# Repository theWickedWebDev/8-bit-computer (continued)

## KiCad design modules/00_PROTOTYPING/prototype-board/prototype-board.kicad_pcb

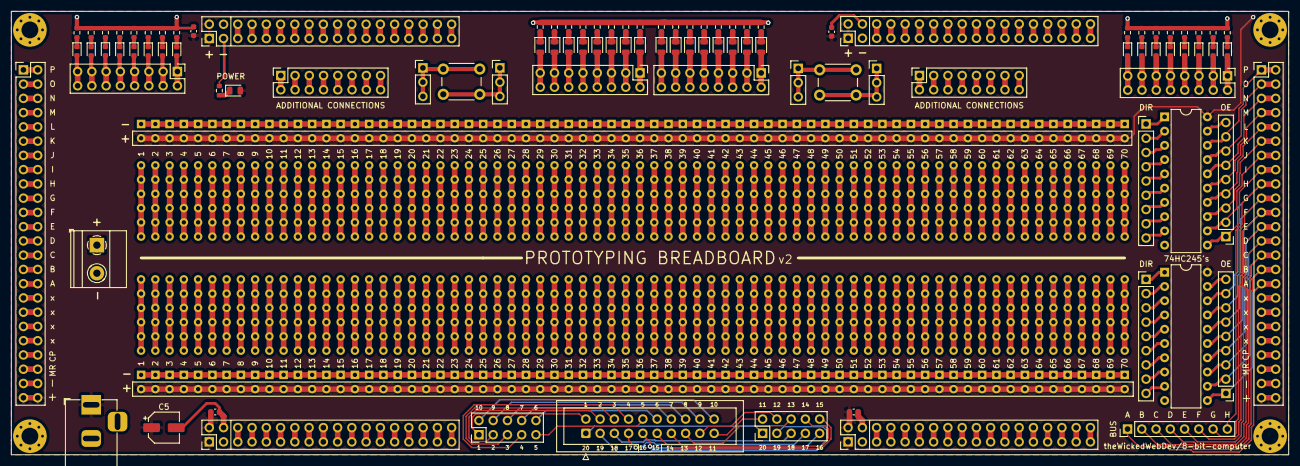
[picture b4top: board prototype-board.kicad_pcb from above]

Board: 2 copper layers, 227.6 x 79.0 mm, 104 parts (0 on the bottom side), 235 nets.

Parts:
C2, C3, C4, C6: 0603B103K500NT; C_0603_1608Metric
C5: SMD-ECAP-5x5.8; CP_Elec_5x5.8
D1, D2, D3, D4, D5, D6, D7, D8, D9, D10, D11, D12, D13, D14, D15, D16, D33: NCD0805R1; LED_0805_2012Metric
D17, D18, D19, D20, D21, D22, D23, D24, D25, D26, D27, D28, D29, D30, D31, D32: 19-217/BHC-ZL1M2RY/3T; LED_0603_1608Metric
J1, J2, J3, J4: Conn_02x08_Male; PinHeader_2x08_P2.54mm_Vertical
J5, J6, J14, J15: Conn_02x18_Odd_Even; PinHeader_2x18_P2.54mm_Vertical
J7: Barrel_Jack; BarrelJack_Horizontal
J8, J9: Conn_02x24_Odd_Even; PinHeader_2x24_P2.54mm_Vertical
J10, J11, J12, J13: Conn_01x09_Male; PinHeader_1x09_P2.54mm_Vertical
J16, J17: Screw_Terminal_02x08; PinSocket_2x08_P2.54mm_Vertical
J18: Screw_Terminal_01x02; TerminalBlock_Phoenix_MKDS-1,5-2_1x02_P5.00mm_Horizontal
J19, J20, J25, J26: Conn_01x03_Male; PinHeader_1x03_P2.54mm_Vertical
J21: Conn_02x20_Odd_Even; IDC-Header_2x10_P2.54mm_Vertical
J22, J23: Conn_02x05_Odd_Even; PinHeader_2x05_P2.54mm_Vertical
J24: Conn_01x08_Male; PinHeader_1x08_P2.54mm_Vertical
SW1, SW2: SW_Push; SW_PUSH_6mm
U1: 6X70X2_breadboard; 6x70
U2, U3: power-rail-breadboard; power-rail-70
U4, U5, U6, U7, U8, U9, U10, U11, U12, U13, U14, U15, U16, U17, U18, U19, U20, U21, U22, U23, U24, U25, U26, U27, U28, U29, U30, U31, U32, U33, U34, U35, U36: 0603WAF1001T5E; R_0603_1608Metric
U39, U68: 74LS245; DIP-20_W7.62mm

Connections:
GND: C2.2, C3.2, C4.2, C5.2, C6.2, J5.3, J5.4, J6.3, J6.4, J7.2, J8.45, J8.46, J9.45, J9.46, J14.3, J14.4, J15.3, J15.4, J18.2, U2.-, U3.-, U4.2, U5.2, U6.2, U7.2, U8.2, U9.2, U10.2, U11.2, U12.2, U13.2, U14.2, U15.2, U16.2, U17.2, U18.2, U19.2, U20.2, U21.2, U22.2, U23.2, U24.2, U25.2, U26.2, U27.2, U28.2, U29.2, U30.2, U31.2, U32.2, U33.2, U34.2, U35.2, U36.2, U39.10, U68.10
unnamed: D1.1, U5.1
unnamed: D1.2, J1.15, J1.16
unnamed: D2.1, U7.1
unnamed: D2.2, J1.13, J1.14
unnamed: D3.1, U9.1
unnamed: D3.2, J1.11, J1.12
unnamed: D4.1, U11.1
unnamed: D4.2, J1.9, J1.10
unnamed: D5.1, U13.1
unnamed: D5.2, J1.7, J1.8
unnamed: D6.1, U15.1
unnamed: D6.2, J1.5, J1.6
unnamed: D7.1, U17.1
unnamed: D7.2, J1.3, J1.4
unnamed: D8.1, U19.1
unnamed: D8.2, J1.1, J1.2
unnamed: D9.1, U4.1
unnamed: D9.2, J2.15, J2.16
unnamed: D10.1, U6.1
unnamed: D10.2, J2.13, J2.14
unnamed: D11.1, U8.1
unnamed: D11.2, J2.11, J2.12
unnamed: D12.1, U10.1
unnamed: D12.2, J2.9, J2.10
unnamed: D13.1, U12.1
unnamed: D13.2, J2.7, J2.8
unnamed: D14.1, U14.1
unnamed: D14.2, J2.5, J2.6
unnamed: D15.1, U16.1
unnamed: D15.2, J2.3, J2.4
unnamed: D16.1, U18.1
unnamed: D16.2, J2.1, J2.2
unnamed: D17.1, U20.1
unnamed: D17.2, J3.15, J3.16
unnamed: D18.1, U21.1
unnamed: D18.2, J3.13, J3.14
unnamed: D19.1, U22.1
unnamed: D19.2, J3.11, J3.12
unnamed: D20.1, U23.1
unnamed: D20.2, J3.9, J3.10
unnamed: D21.1, U24.1
unnamed: D21.2, J3.7, J3.8
unnamed: D22.1, U25.1
unnamed: D22.2, J3.5, J3.6
unnamed: D23.1, U26.1
unnamed: D23.2, J3.3, J3.4
unnamed: D24.1, U27.1
unnamed: D24.2, J3.1, J3.2
unnamed: D25.1, U28.1
unnamed: D25.2, J4.15, J4.16
unnamed: D26.1, U29.1
unnamed: D26.2, J4.13, J4.14
unnamed: D27.1, U30.1
unnamed: D27.2, J4.11, J4.12
unnamed: D28.1, U31.1
unnamed: D28.2, J4.9, J4.10
unnamed: D29.1, U32.1
unnamed: D29.2, J4.7, J4.8
unnamed: D30.1, U33.1
unnamed: D30.2, J4.5, J4.6
unnamed: D31.1, U34.1
unnamed: D31.2, J4.3, J4.4
unnamed: D32.1, U35.1
unnamed: D32.2, J4.1, J4.2
unnamed: D33.1, U36.1
unnamed: J5.5, J5.6
unnamed: J5.7, J5.8
unnamed: J5.9, J5.10
unnamed: J5.11, J5.12
unnamed: J5.13, J5.14
unnamed: J5.15, J5.16
unnamed: J5.17, J5.18
unnamed: J5.19, J5.20
unnamed: J5.21, J5.22
unnamed: J5.23, J5.24
unnamed: J5.25, J5.26
unnamed: J5.27, J5.28
unnamed: J5.29, J5.30
unnamed: J5.31, J5.32
unnamed: J5.33, J5.34
unnamed: J5.35, J5.36
unnamed: J6.5, J6.6
unnamed: J6.7, J6.8
unnamed: J6.9, J6.10
unnamed: J6.11, J6.12
unnamed: J6.13, J6.14
unnamed: J6.15, J6.16
unnamed: J6.17, J6.18
unnamed: J6.19, J6.20
unnamed: J6.21, J6.22
unnamed: J6.23, J6.24
unnamed: J6.25, J6.26
unnamed: J6.27, J6.28
unnamed: J6.29, J6.30
unnamed: J6.31, J6.32
unnamed: J6.33, J6.34
unnamed: J6.35, J6.36
unnamed: J8.33, J8.34
unnamed: J8.35, J8.36
unnamed: J8.37, J8.38
unnamed: J8.39, J8.40
unnamed: J8.41, J8.42
unnamed: J8.43, J8.44
unnamed: J9.1, J9.2
unnamed: J9.3, J9.4
unnamed: J9.5, J9.6
unnamed: J9.7, J9.8
unnamed: J9.9, J9.10
unnamed: J9.11, J9.12
unnamed: J9.13, J9.14
unnamed: J9.15, J9.16
unnamed: J9.17, J9.18
unnamed: J9.19, J9.20
unnamed: J9.21, J9.22
unnamed: J9.23, J9.24
unnamed: J9.25, J9.26
unnamed: J9.27, J9.28
unnamed: J9.29, J9.30
unnamed: J9.31, J9.32
unnamed: J9.33, J9.34
unnamed: J9.35, J9.36
unnamed: J9.37, J9.38
unnamed: J9.39, J9.40
unnamed: J9.41, J9.42
unnamed: J9.43, J9.44
unnamed: J10.1, U68.1
unnamed: J10.2, U68.2
unnamed: J10.3, U68.3
unnamed: J10.4, U68.4
unnamed: J10.5, U68.5
unnamed: J10.6, U68.6
unnamed: J10.7, U68.7
unnamed: J10.8, U68.8
unnamed: J10.9, U68.9
unnamed: J8.15, J8.16, J11.1, U68.11
unnamed: J8.13, J8.14, J11.2, U68.12
unnamed: J8.11, J8.12, J11.3, U68.13
unnamed: J8.9, J8.10, J11.4, U68.14
unnamed: J8.7, J8.8, J11.5, U68.15
unnamed: J8.5, J8.6, J11.6, U68.16
unnamed: J8.3, J8.4, J11.7, U68.17
unnamed: J8.1, J8.2, J11.8, U68.18
unnamed: J11.9, U68.19
unnamed: J12.1, U39.1
unnamed: J12.2, U39.2
unnamed: J12.3, U39.3
unnamed: J12.4, U39.4
unnamed: J12.5, U39.5
unnamed: J12.6, U39.6
unnamed: J12.7, U39.7
unnamed: J12.8, U39.8
unnamed: J12.9, U39.9
unnamed: J8.31, J8.32, J13.1, J24.1, U39.11
unnamed: J8.29, J8.30, J13.2, J24.2, U39.12
unnamed: J8.27, J8.28, J13.3, J24.3, U39.13
unnamed: J8.25, J8.26, J13.4, J24.4, U39.14
unnamed: J8.23, J8.24, J13.5, J24.5, U39.15
unnamed: J8.21, J8.22, J13.6, J24.6, U39.16
unnamed: J8.19, J8.20, J13.7, J24.7, U39.17
unnamed: J8.17, J8.18, J13.8, J24.8, U39.18
unnamed: J13.9, U39.19
unnamed: J14.5, J14.6
unnamed: J14.7, J14.8
unnamed: J14.9, J14.10
unnamed: J14.11, J14.12
unnamed: J14.13, J14.14
unnamed: J14.15, J14.16
unnamed: J14.17, J14.18
unnamed: J14.19, J14.20
unnamed: J14.21, J14.22
unnamed: J14.23, J14.24
unnamed: J14.25, J14.26
unnamed: J14.27, J14.28
unnamed: J14.29, J14.30
unnamed: J14.31, J14.32
unnamed: J14.33, J14.34
unnamed: J14.35, J14.36
unnamed: J15.5, J15.6
unnamed: J15.7, J15.8
unnamed: J15.9, J15.10
unnamed: J15.11, J15.12
unnamed: J15.13, J15.14
unnamed: J15.15, J15.16
unnamed: J15.17, J15.18
unnamed: J15.19, J15.20
unnamed: J15.21, J15.22
unnamed: J15.23, J15.24
unnamed: J15.25, J15.26
unnamed: J15.27, J15.28
unnamed: J15.29, J15.30
unnamed: J15.31, J15.32
unnamed: J15.33, J15.34
unnamed: J15.35, J15.36
unnamed: J16.1, J16.2
unnamed: J16.3, J16.4
unnamed: J16.5, J16.6
unnamed: J16.7, J16.8
unnamed: J16.9, J16.10
unnamed: J16.11, J16.12
unnamed: J16.13, J16.14
unnamed: J16.15, J16.16
unnamed: J17.1, J17.2
unnamed: J17.3, J17.4
unnamed: J17.5, J17.6
unnamed: J17.7, J17.8
unnamed: J17.9, J17.10
unnamed: J17.11, J17.12
unnamed: J17.13, J17.14
unnamed: J17.15, J17.16
unnamed: J19.1, J19.2, J19.3, SW1.2
unnamed: J20.1, J20.2, J20.3, SW1.1
unnamed: J21.1, J23.1
unnamed: J21.2, J22.1
unnamed: J21.3, J23.3
unnamed: J21.4, J22.3
unnamed: J21.5, J23.5
unnamed: J21.6, J22.5
unnamed: J21.7, J23.7
unnamed: J21.8, J22.7
unnamed: J21.9, J23.9
unnamed: J21.10, J22.9
unnamed: J21.11, J23.10
unnamed: J21.12, J22.10
unnamed: J21.13, J23.8
unnamed: J21.14, J22.8
unnamed: J21.15, J23.6
unnamed: J21.16, J22.6
unnamed: J21.17, J23.4
unnamed: J21.18, J22.4
unnamed: J21.19, J23.2
unnamed: J21.20, J22.2
unnamed: J25.1, J25.2, J25.3, SW2.1
unnamed: J26.1, J26.2, J26.3, SW2.2
VCC: C2.1, C3.1, C4.1, C5.1, C6.1, D33.2, J5.1, J5.2, J6.1, J6.2, J7.1, J8.47, J8.48, J9.47, J9.48, J14.1, J14.2, J15.1, J15.2, J18.1, U2.+, U3.+, U39.20, U68.20

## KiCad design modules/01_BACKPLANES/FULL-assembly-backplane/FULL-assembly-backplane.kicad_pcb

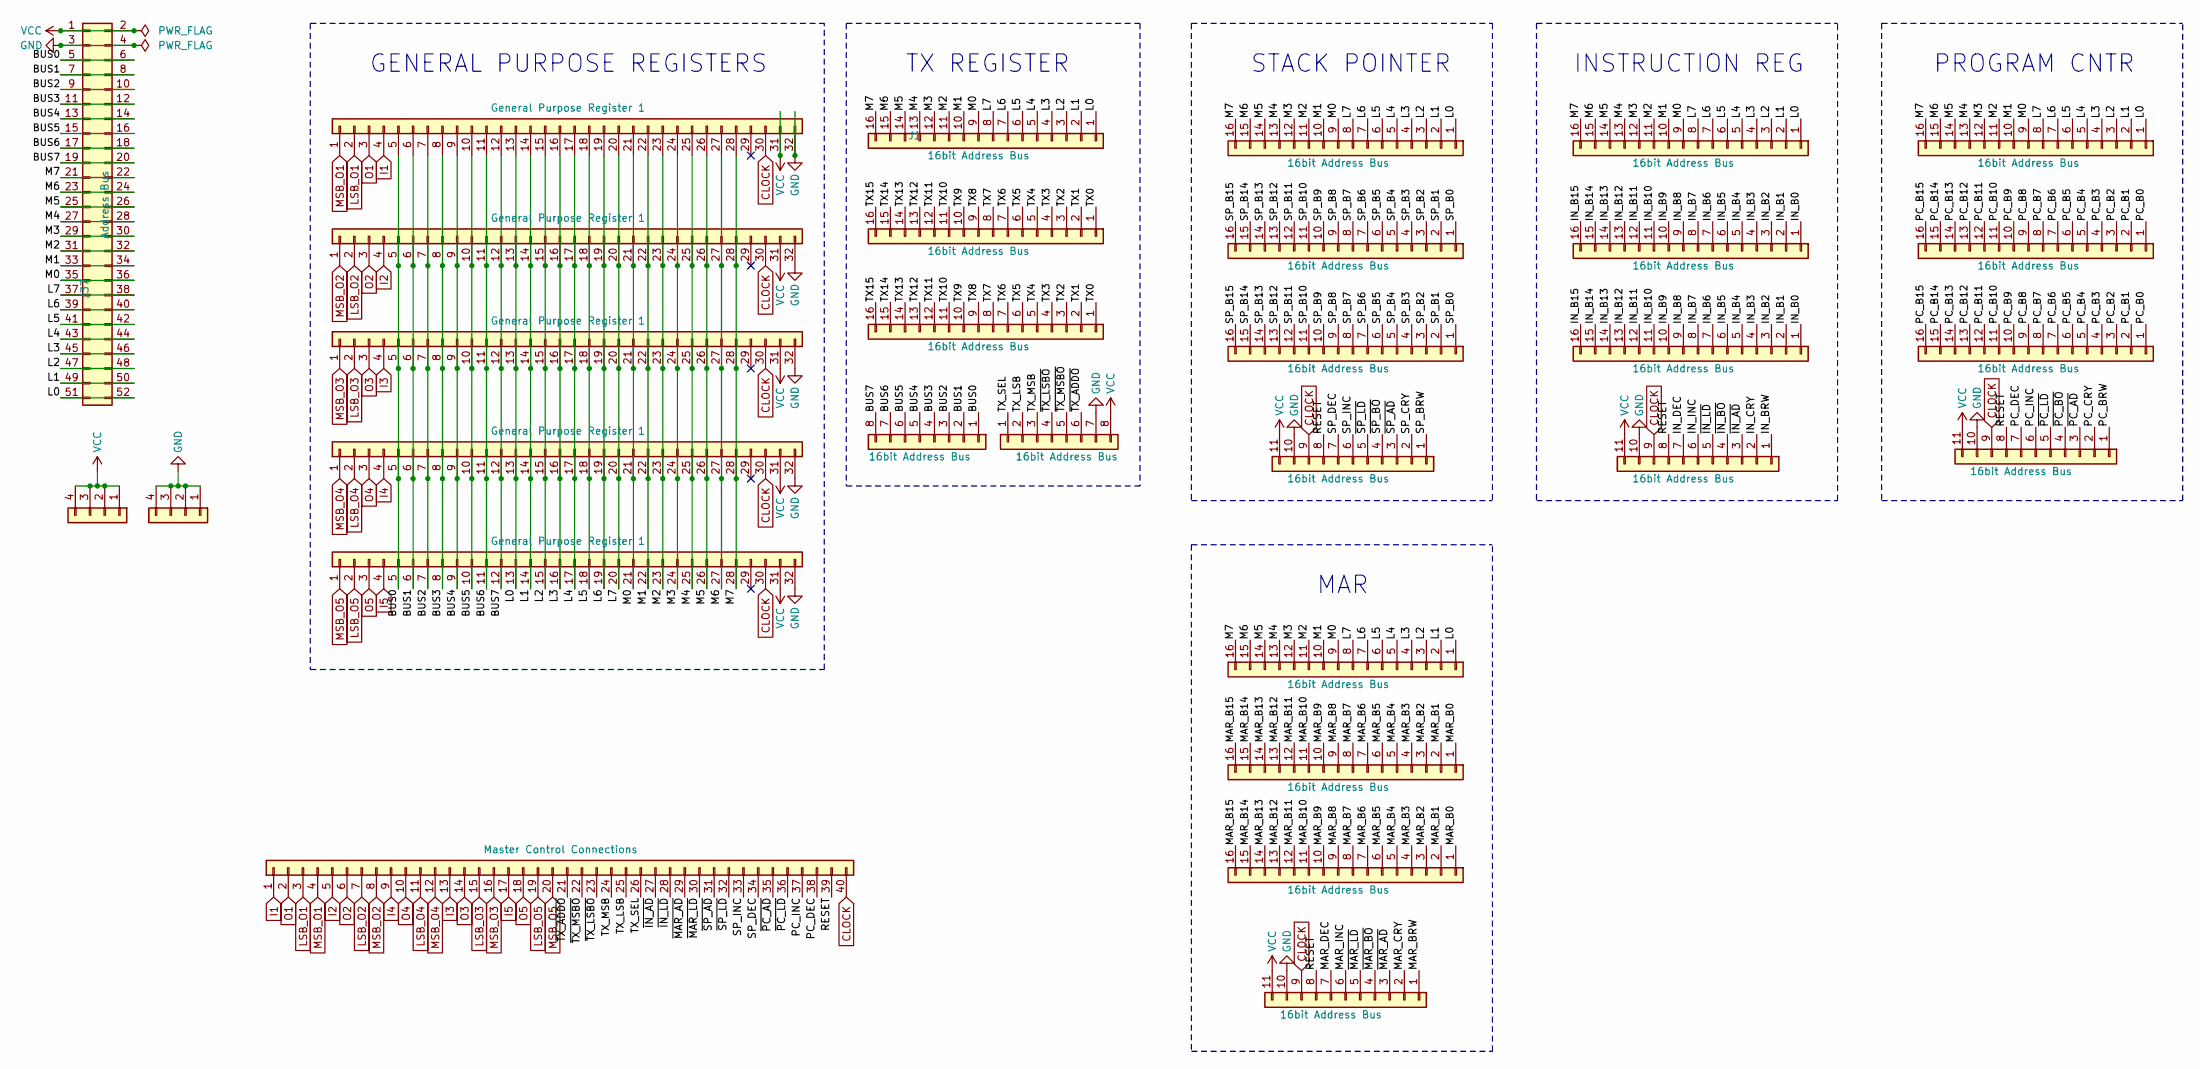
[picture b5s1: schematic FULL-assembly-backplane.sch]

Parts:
J1, J2, J5, J6, J7, J8, J9, J10, J11, J12, J13, J14, J15, J16, J17: Conn_01x16; PinHeader_1x16_P2.54mm_Vertical
J3, J4: Conn_01x08; PinHeader_1x08_P2.54mm_Vertical
J18, J19, J20, J21: Conn_01x11; PinHeader_1x11_P2.54mm_Vertical
J22: Conn_01x37; PinSocket_1x40_P2.54mm_Vertical
J23, J24: Conn_01x04; PinHeader_1x04_P2.54mm_Vertical
J32, J33, J34, J35, J36: Conn_01x32; PinSocket_1x32_P2.54mm_Vertical
J37: Conn_01x26; PinHeader_2x26_P2.54mm_Vertical

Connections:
/BUS0: J3.1, J32.5, J33.5, J34.5, J35.5, J36.5, J37.5, J37.6
/BUS1: J3.2, J32.6, J33.6, J34.6, J35.6, J36.6, J37.7, J37.8
/BUS2: J3.3, J32.7, J33.7, J34.7, J35.7, J36.7, J37.9, J37.10
/BUS3: J3.4, J32.8, J33.8, J34.8, J35.8, J36.8, J37.11, J37.12
/BUS4: J3.5, J32.9, J33.9, J34.9, J35.9, J36.9, J37.13, J37.14
/BUS5: J3.6, J32.10, J33.10, J34.10, J35.10, J36.10, J37.15, J37.16
/BUS6: J3.7, J32.11, J33.11, J34.11, J35.11, J36.11, J37.17, J37.18
/BUS7: J3.8, J32.12, J33.12, J34.12, J35.12, J36.12, J37.19, J37.20
/IN_B0: J10.1, J11.1
/IN_B1: J10.2, J11.2
/IN_B2: J10.3, J11.3
/IN_B3: J10.4, J11.4
/IN_B4: J10.5, J11.5
/IN_B5: J10.6, J11.6
/IN_B6: J10.7, J11.7
/IN_B7: J10.8, J11.8
/IN_B8: J10.9, J11.9
/IN_B9: J10.10, J11.10
/IN_B10: J10.11, J11.11
/IN_B11: J10.12, J11.12
/IN_B12: J10.13, J11.13
/IN_B13: J10.14, J11.14
/IN_B14: J10.15, J11.15
/IN_B15: J10.16, J11.16
/IN_BRW: J19.1
/IN_CRY: J19.2
/IN_DEC: J19.7
/IN_INC: J19.6
/L0: J1.1, J6.1, J9.1, J12.1, J15.1, J32.13, J33.13, J34.13, J35.13, J36.13, J37.51, J37.52
/L1: J1.2, J6.2, J9.2, J12.2, J15.2, J32.14, J33.14, J34.14, J35.14, J36.14, J37.49, J37.50
/L2: J1.3, J6.3, J9.3, J12.3, J15.3, J32.15, J33.15, J34.15, J35.15, J36.15, J37.47, J37.48
/L3: J1.4, J6.4, J9.4, J12.4, J15.4, J32.16, J33.16, J34.16, J35.16, J36.16, J37.45, J37.46
/L4: J1.5, J6.5, J9.5, J12.5, J15.5, J32.17, J33.17, J34.17, J35.17, J36.17, J37.43, J37.44
/L5: J1.6, J6.6, J9.6, J12.6, J15.6, J32.18, J33.18, J34.18, J35.18, J36.18, J37.41, J37.42
/L6: J1.7, J6.7, J9.7, J12.7, J15.7, J32.19, J33.19, J34.19, J35.19, J36.19, J37.39, J37.40
/L7: J1.8, J6.8, J9.8, J12.8, J15.8, J32.20, J33.20, J34.20, J35.20, J36.20, J37.37, J37.38
/M0: J1.9, J6.9, J9.9, J12.9, J15.9, J32.21, J33.21, J34.21, J35.21, J36.21, J37.35, J37.36
/M1: J1.10, J6.10, J9.10, J12.10, J15.10, J32.22, J33.22, J34.22, J35.22, J36.22, J37.33, J37.34
/M2: J1.11, J6.11, J9.11, J12.11, J15.11, J32.23, J33.23, J34.23, J35.23, J36.23, J37.31, J37.32
/M3: J1.12, J6.12, J9.12, J12.12, J15.12, J32.24, J33.24, J34.24, J35.24, J36.24, J37.29, J37.30
/M4: J1.13, J6.13, J9.13, J12.13, J15.13, J32.25, J33.25, J34.25, J35.25, J36.25, J37.27, J37.28
/M5: J1.14, J6.14, J9.14, J12.14, J15.14, J32.26, J33.26, J34.26, J35.26, J36.26, J37.25, J37.26
/M6: J1.15, J6.15, J9.15, J12.15, J15.15, J32.27, J33.27, J34.27, J35.27, J36.27, J37.23, J37.24
/M7: J1.16, J6.16, J9.16, J12.16, J15.16, J32.28, J33.28, J34.28, J35.28, J36.28, J37.21, J37.22
/MAR_B0: J16.1, J17.1
/MAR_B1: J16.2, J17.2
/MAR_B2: J16.3, J17.3
/MAR_B3: J16.4, J17.4
/MAR_B4: J16.5, J17.5
/MAR_B5: J16.6, J17.6
/MAR_B6: J16.7, J17.7
/MAR_B7: J16.8, J17.8
/MAR_B8: J16.9, J17.9
/MAR_B9: J16.10, J17.10
/MAR_B10: J16.11, J17.11
/MAR_B11: J16.12, J17.12
/MAR_B12: J16.13, J17.13
/MAR_B13: J16.14, J17.14
/MAR_B14: J16.15, J17.15
/MAR_B15: J16.16, J17.16
/MAR_BRW: J20.1
/MAR_CRY: J20.2
/MAR_DEC: J20.7
/MAR_INC: J20.6
/PC_B0: J13.1, J14.1
/PC_B1: J13.2, J14.2
/PC_B2: J13.3, J14.3
/PC_B3: J13.4, J14.4
/PC_B4: J13.5, J14.5
/PC_B5: J13.6, J14.6
/PC_B6: J13.7, J14.7
/PC_B7: J13.8, J14.8
/PC_B8: J13.9, J14.9
/PC_B9: J13.10, J14.10
/PC_B10: J13.11, J14.11
/PC_B11: J13.12, J14.12
/PC_B12: J13.13, J14.13
/PC_B13: J13.14, J14.14
/PC_B14: J13.15, J14.15
/PC_B15: J13.16, J14.16
/PC_BRW: J21.1
/PC_CRY: J21.2
/PC_DEC: J21.7, J22.38
/PC_INC: J21.6, J22.37
/RESET: J18.8, J19.8, J20.8, J21.8, J22.39
/SP_B0: J7.1, J8.1
/SP_B1: J7.2, J8.2
/SP_B2: J7.3, J8.3
/SP_B3: J7.4, J8.4
/SP_B4: J7.5, J8.5
/SP_B5: J7.6, J8.6
/SP_B6: J7.7, J8.7
/SP_B7: J7.8, J8.8
/SP_B8: J7.9, J8.9
/SP_B9: J7.10, J8.10
/SP_B10: J7.11, J8.11
/SP_B11: J7.12, J8.12
/SP_B12: J7.13, J8.13
/SP_B13: J7.14, J8.14
/SP_B14: J7.15, J8.15
/SP_B15: J7.16, J8.16
/SP_BRW: J18.1
/SP_CRY: J18.2
/SP_DEC: J18.7, J22.34
/SP_INC: J18.6, J22.33
/TX0: J2.1, J5.1
/TX1: J2.2, J5.2
/TX2: J2.3, J5.3
/TX3: J2.4, J5.4
/TX4: J2.5, J5.5
/TX5: J2.6, J5.6
/TX6: J2.7, J5.7
/TX7: J2.8, J5.8
/TX8: J2.9, J5.9
/TX9: J2.10, J5.10
/TX10: J2.11, J5.11
/TX11: J2.12, J5.12
/TX12: J2.13, J5.13
/TX13: J2.14, J5.14
/TX14: J2.15, J5.15
/TX15: J2.16, J5.16
/TX_LSB: J4.2, J22.25
/TX_MSB: J4.3, J22.24
/TX_SEL: J4.1, J22.26
/~IN_AD: J19.3, J22.27
/~IN_BO: J19.4
/~IN_LD: J19.5, J22.28
/~MAR_AD: J20.3, J22.29
/~MAR_BO: J20.4
/~MAR_LD: J20.5, J22.30
/~PC_AD: J21.3, J22.35
/~PC_BO: J21.4
/~PC_LD: J21.5, J22.36
/~SP_AD: J18.3, J22.31
/~SP_BO: J18.4
/~SP_LD: J18.5, J22.32
/~TX_ADDO: J4.6, J22.21
/~TX_LSBO: J4.4, J22.23
/~TX_MSBO: J4.5, J22.22
CLOCK: J18.9, J19.9, J20.9, J21.9, J22.40, J32.30, J33.30, J34.30, J35.30, J36.30
GND: J4.7, J18.10, J19.10, J20.10, J21.10, J24.1, J24.2, J24.3, J24.4, J32.32, J33.32, J34.32, J35.32, J36.32, J37.3, J37.4
I1: J22.1, J32.4
I2: J22.5, J33.4
I3: J22.13, J34.4
I4: J22.9, J35.4
I5: J22.17, J36.4
LSB_O1: J22.3, J32.2
LSB_O2: J22.7, J33.2
LSB_O3: J22.15, J34.2
LSB_O4: J22.11, J35.2
LSB_O5: J22.19, J36.2
MSB_O1: J22.4, J32.1
MSB_O2: J22.8, J33.1
MSB_O3: J22.16, J34.1
MSB_O4: J22.12, J35.1
MSB_O5: J22.20, J36.1
O1: J22.2, J32.3
O2: J22.6, J33.3
O3: J22.14, J34.3
O4: J22.10, J35.3
O5: J22.18, J36.3
VCC: J4.8, J18.11, J19.11, J20.11, J21.11, J23.1, J23.2, J23.3, J23.4, J32.31, J33.31, J34.31, J35.31, J36.31, J37.1, J37.2

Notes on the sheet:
GENERAL PURPOSE REGISTERS
TX REGISTER
STACK POINTER
INSTRUCTION REG
PROGRAM CNTR
MAR

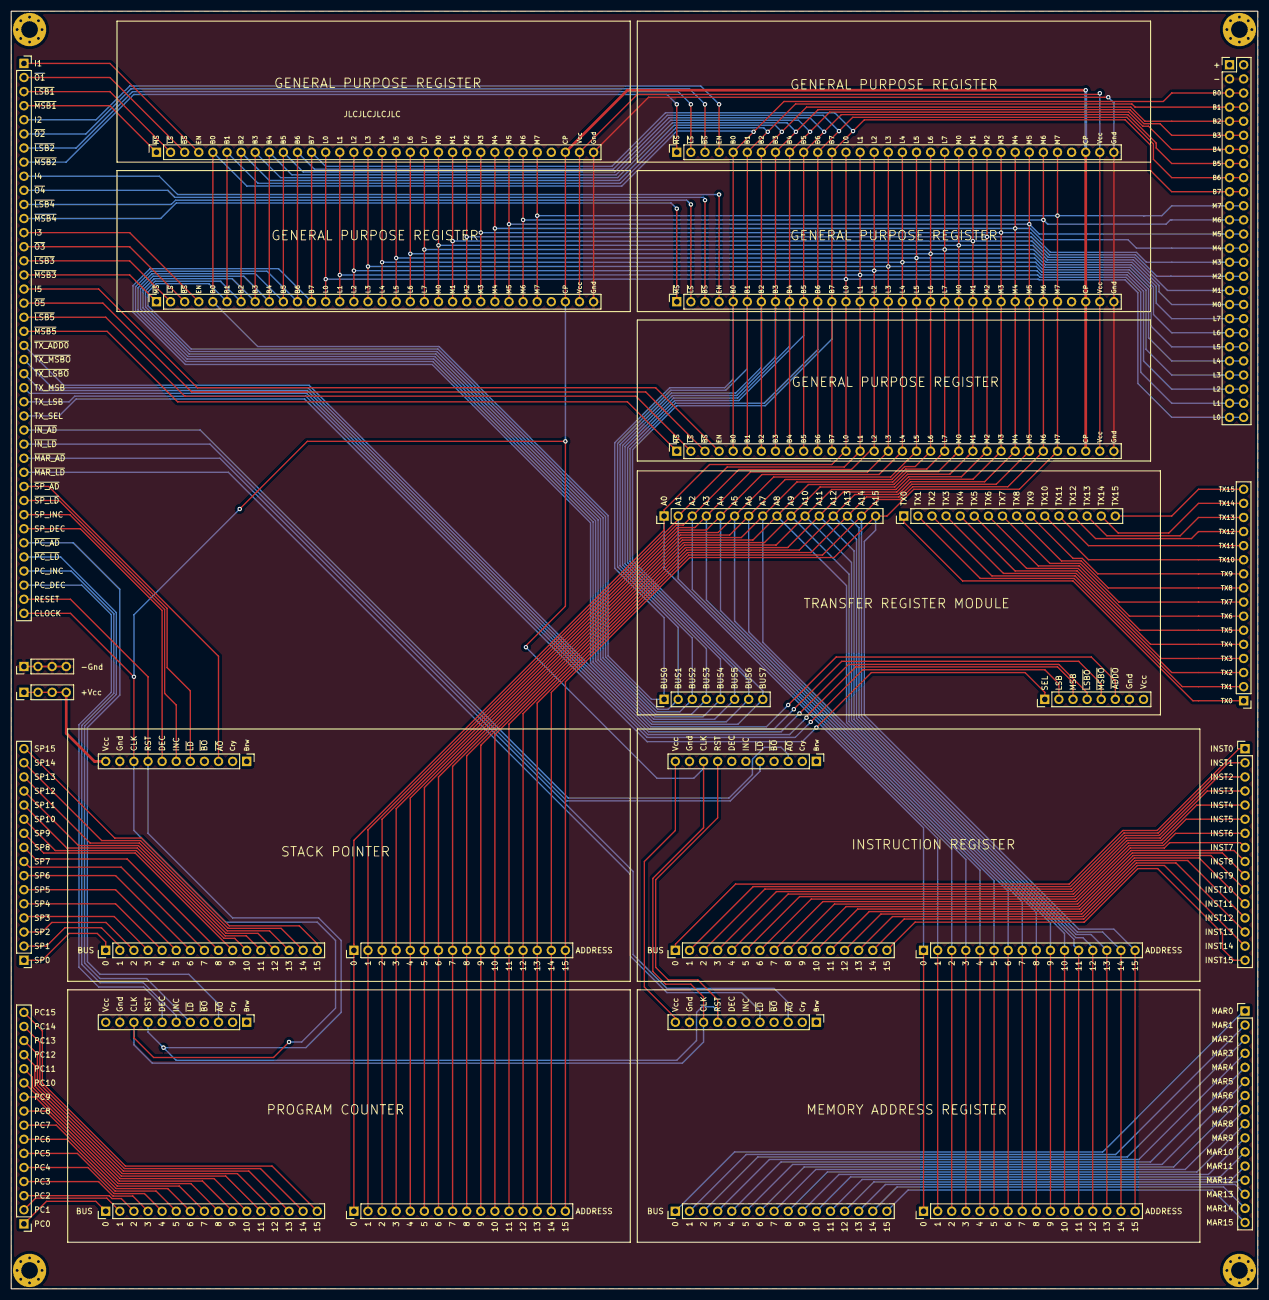
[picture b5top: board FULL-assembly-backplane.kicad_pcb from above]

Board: 2 copper layers, 224.5 x 230.1 mm, 30 parts (0 on the bottom side), 146 nets.

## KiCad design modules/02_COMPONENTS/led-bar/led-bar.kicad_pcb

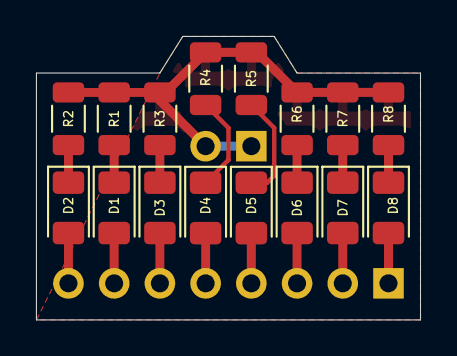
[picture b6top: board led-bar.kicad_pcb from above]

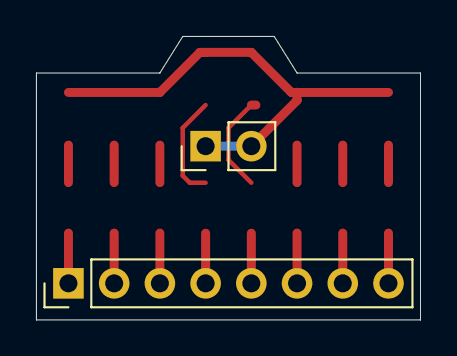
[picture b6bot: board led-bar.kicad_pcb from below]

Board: 2 copper layers, 21.3 x 15.7 mm, 18 parts (2 on the bottom side), 17 nets.

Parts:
D1, D2, D3, D4, D5, D6, D7, D8: 19-217/GHC-YR1S2/3T; LED_1206_3216Metric
J1: Conn_01x08_Male; PinHeader_1x08_P2.54mm_Vertical
J2: Conn_01x02_Male; PinHeader_1x02_P2.54mm_Vertical
R1, R2, R3, R4, R5, R6, R7, R8: 0402WGF1001TCE; R_1206_3216Metric

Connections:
GND: J2.1, J2.2, R1.2, R2.2, R3.2, R4.2, R5.2, R6.2, R7.2, R8.2
unnamed: D1.1, R1.1
unnamed: D1.2, J1.7
unnamed: D2.1, R2.1
unnamed: D2.2, J1.8
unnamed: D3.1, R3.1
unnamed: D3.2, J1.6
unnamed: D4.1, R4.1
unnamed: D4.2, J1.5
unnamed: D5.1, R5.1
unnamed: D5.2, J1.4
unnamed: D6.1, R6.1
unnamed: D6.2, J1.3
unnamed: D7.1, R7.1
unnamed: D7.2, J1.2
unnamed: D8.1, R8.1
unnamed: D8.2, J1.1

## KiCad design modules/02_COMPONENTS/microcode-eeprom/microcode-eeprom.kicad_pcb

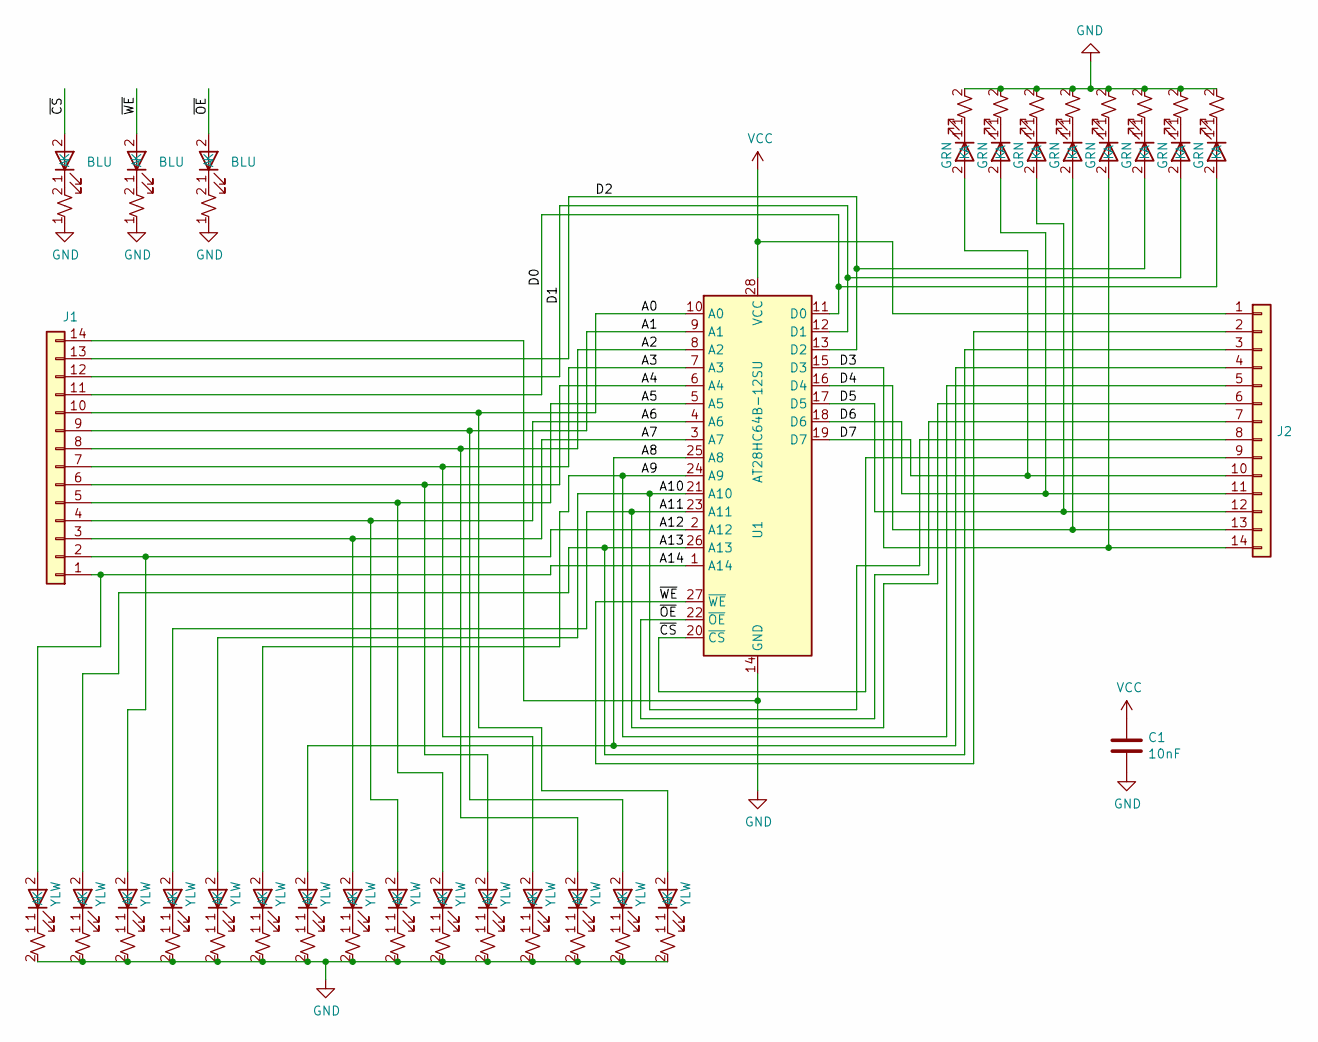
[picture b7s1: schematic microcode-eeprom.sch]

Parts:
C1: 0603B103K500NT; C_0603_1608Metric
J1, J2: Conn_01x14; PinHeader_1x14_P2.54mm_Vertical
U1: AT28HC64B-12SU; SOIC-28W_7.5x17.9mm_P1.27mm
U2, U4, U6, U8, U10, U12, U14, U16, U18, U20, U22, U24, U26, U28, U30: 19-213_Y2C-CQ2R2L_3T(CY); LED_0603_1608Metric
U3, U5, U7, U9, U11, U13, U15, U17, U19, U21, U23, U25, U27, U29, U31, U33, U35, U37, U39, U41, U43, U45, U47, U49, U51, U53: 0603WAF1001T5E; R_0603_1608Metric
U32, U34, U36, U38, U40, U42, U44, U46: 19-217_GHC-YR1S2_3T; LED_0603_1608Metric
U48, U50, U52: 19-217_BHC-ZL1M2RY_3T; LED_0603_1608Metric

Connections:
/A0: J1.10, U1.10 (A0), U30.2 (A)
/A1: J1.9, U1.9 (A1), U28.2 (A)
/A2: J1.8, U1.8 (A2), U26.2 (A)
/A3: J1.7, U1.7 (A3), U24.2 (A)
/A4: J1.6, U1.6 (A4), U22.2 (A)
/A5: J1.5, U1.5 (A5), U20.2 (A)
/A6: J1.4, U1.4 (A6), U18.2 (A)
/A7: J1.3, U1.3 (A7), U16.2 (A)
/A8: J2.4, U1.25 (A8), U14.2 (A)
/A9: J2.5, U1.24 (A9), U12.2 (A)
/A10: J2.8, U1.21 (A10), U10.2 (A)
/A11: J2.6, U1.23 (A11), U8.2 (A)
/A12: J1.2, U1.2 (A12), U6.2 (A)
/A13: J2.3, U1.26 (A13), U4.2 (A)
/A14: J1.1, U1.1 (A14), U2.2 (A)
/D0: J1.11, U1.11 (D0), U32.2 (A)
/D1: J1.12, U1.12 (D1), U34.2 (A)
/D2: J1.13, U1.13 (D2), U36.2 (A)
/D3: J2.14, U1.15 (D3), U38.2 (A)
/D4: J2.13, U1.16 (D4), U40.2 (A)
/D5: J2.12, U1.17 (D5), U42.2 (A)
/D6: J2.11, U1.18 (D6), U44.2 (A)
/D7: J2.10, U1.19 (D7), U46.2 (A)
/~CS: J2.9, U1.20 (~CS), U48.2 (A)
/~OE: J2.7, U1.22 (~OE), U52.2 (A)
/~WE: J2.2, U1.27 (~WE), U50.2 (A)
GND: C1.2, J1.14, U1.14 (GND), U3.2, U5.2, U7.2, U9.2, U11.2, U13.2, U15.2, U17.2, U19.2, U21.2, U23.2, U25.2, U27.2, U29.2, U31.2, U33.2, U35.2, U37.2, U39.2, U41.2, U43.2, U45.2, U47.2, U49.1, U51.1, U53.1
unnamed: U2.1 (K), U3.1
unnamed: U4.1 (K), U5.1
unnamed: U6.1 (K), U7.1
unnamed: U8.1 (K), U9.1
unnamed: U10.1 (K), U11.1
unnamed: U12.1 (K), U13.1
unnamed: U14.1 (K), U15.1
unnamed: U16.1 (K), U17.1
unnamed: U18.1 (K), U19.1
unnamed: U20.1 (K), U21.1
unnamed: U22.1 (K), U23.1
unnamed: U24.1 (K), U25.1
unnamed: U26.1 (K), U27.1
unnamed: U28.1 (K), U29.1
unnamed: U30.1 (K), U31.1
unnamed: U32.1 (K), U33.1
unnamed: U34.1 (K), U35.1
unnamed: U36.1 (K), U37.1
unnamed: U38.1 (K), U39.1
unnamed: U40.1 (K), U41.1
unnamed: U42.1 (K), U43.1
unnamed: U44.1 (K), U45.1
unnamed: U46.1 (K), U47.1
unnamed: U48.1 (K), U49.2
unnamed: U50.1 (K), U51.2
unnamed: U52.1 (K), U53.2
VCC: C1.1, J2.1, U1.28 (VCC)

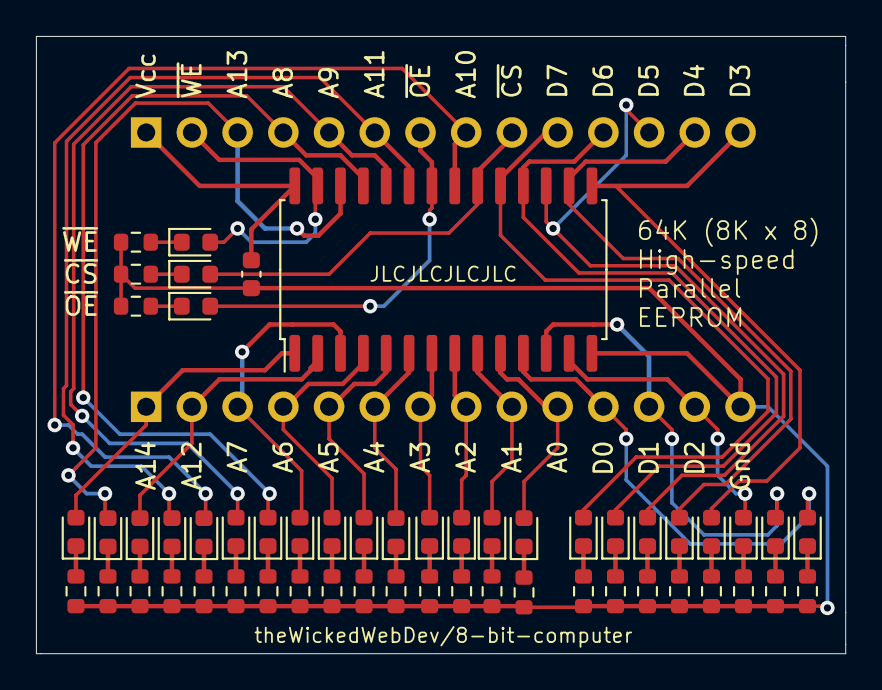
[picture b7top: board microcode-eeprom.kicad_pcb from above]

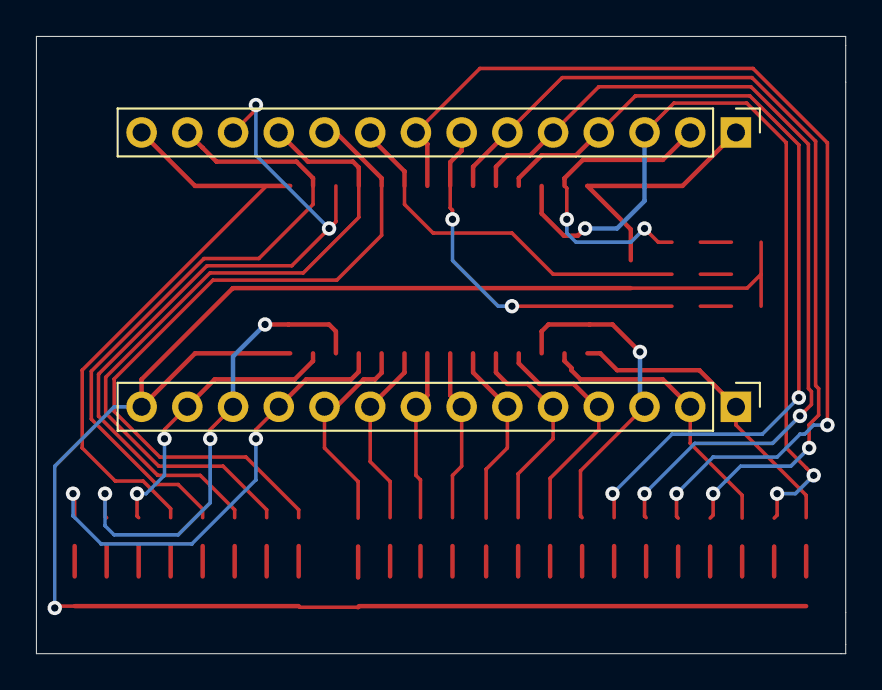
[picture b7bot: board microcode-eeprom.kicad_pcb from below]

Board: 2 copper layers, 45.0 x 34.3 mm, 56 parts (2 on the bottom side), 54 nets.
